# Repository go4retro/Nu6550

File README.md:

# Nu6550

Replacement for the MOS 6550 1kbx4 SRAM using modern components.

## Introduction

## Technical Details

## License
Copyright (C) 2019-20  RETRO Innovations

These files are free designs; you can redistribute them and/or modify
them under the terms of the Creative Commons Attribution-ShareAlike 
4.0 International License.

You should have received a copy of the license along with this
work. If not, see <http://creativecommons.org/licenses/by-sa/4.0/>.

These files are distributed in the hope that they will be useful,
but WITHOUT ANY WARRANTY; without even the implied warranty of
MERCHANTABILITY or FITNESS FOR A PARTICULAR PURPOSE.  See the
license for more details.

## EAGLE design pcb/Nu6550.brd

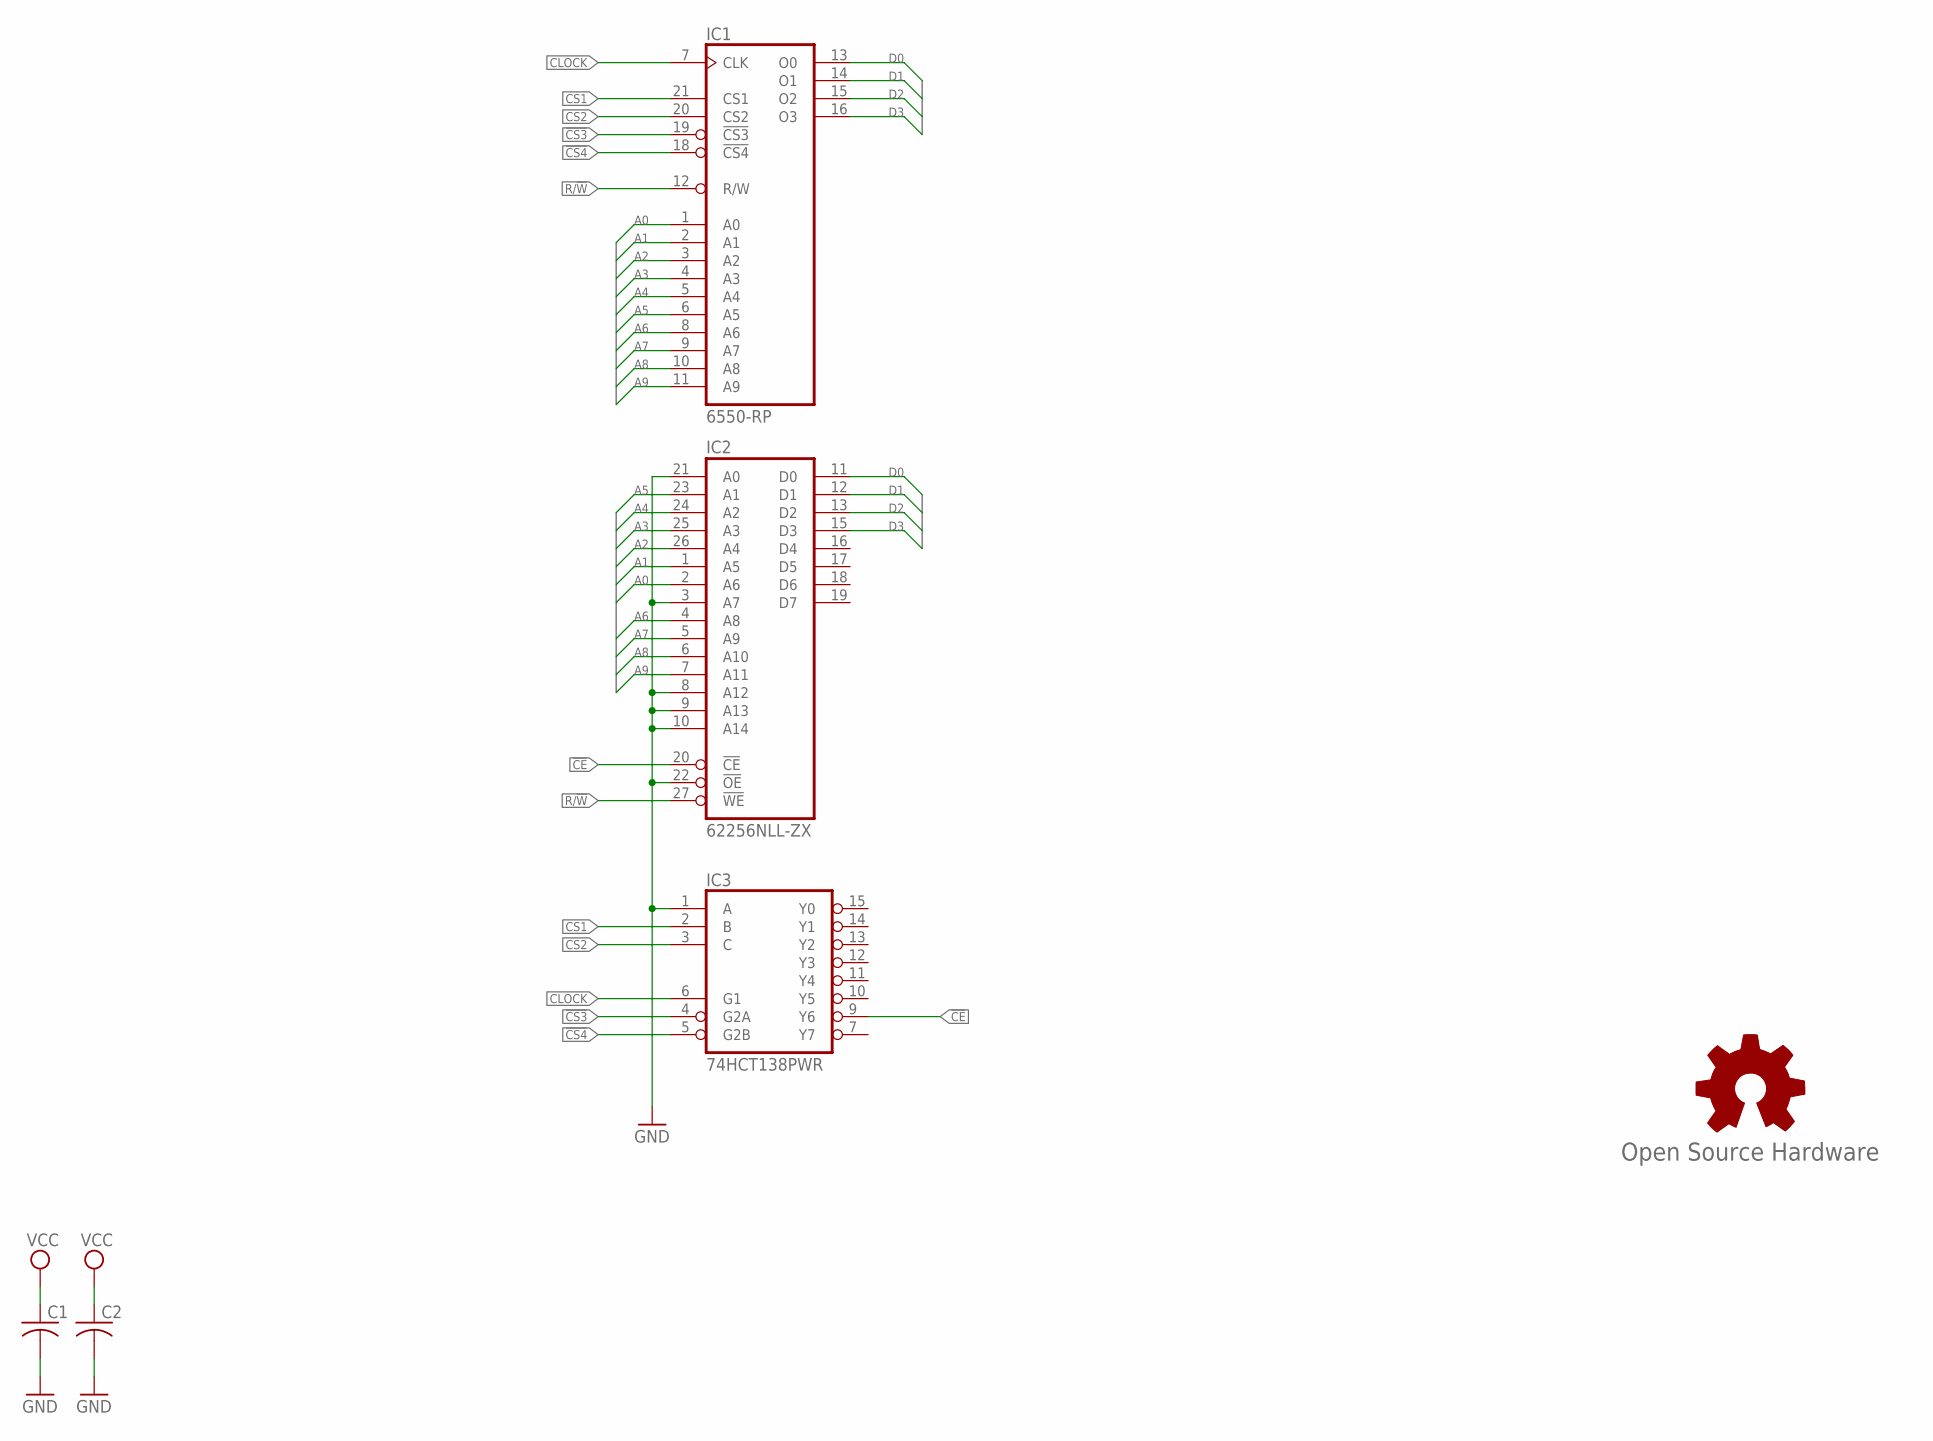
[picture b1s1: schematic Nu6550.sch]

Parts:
C1, C2: C-USC0402; C0402
GOLD_ORB_SM1: Open Source Hardware; OSHW_5MM
IC1: 6550-RP; DIL22/4-ROUNDPAD
IC2: 62256NLL-ZX; TSOP1-28
IC3: 74HCT138PWR; TSSOP16

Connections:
!CE: IC2.20 (!CE), IC3.9 (Y6)
!CS3: IC1.19 (!CS3), IC3.4 (G2A)
!CS4: IC1.18 (!CS4), IC3.5 (G2B)
A0: IC1.1 (A0), IC2.2 (A6)
A1: IC1.2 (A1), IC2.1 (A5)
A2: IC1.3 (A2), IC2.26 (A4)
A3: IC1.4 (A3), IC2.25 (A3)
A4: IC1.5 (A4), IC2.24 (A2)
A5: IC1.6 (A5), IC2.23 (A1)
A6: IC1.8 (A6), IC2.4 (A8)
A7: IC1.9 (A7), IC2.5 (A9)
A8: IC1.10 (A8), IC2.6 (A10)
A9: IC1.11 (A9), IC2.7 (A11)
CLOCK: IC1.7 (CLK), IC3.6 (G1)
CS1: IC1.21 (CS1), IC3.2 (B)
CS2: IC1.20 (CS2), IC3.3 (C)
D0: IC1.13 (O0), IC2.11 (D0)
D1: IC1.14 (O1), IC2.12 (D1)
D2: IC1.15 (O2), IC2.13 (D2)
D3: IC1.16 (O3), IC2.15 (D3)
GND: C1.2, C2.2, IC1.22 (GND), IC2.3 (A7), IC2.8 (A12), IC2.9 (A13), IC2.10 (A14), IC2.14 (GND), IC2.21 (A0), IC2.22 (!OE), IC3.1 (A), IC3.8 (GND)
R/!W: IC1.12 (R/W), IC2.27 (!WE)
VCC: C1.1, C2.1, IC1.17 (VCC), IC2.28 (VCC), IC3.16 (VCC)

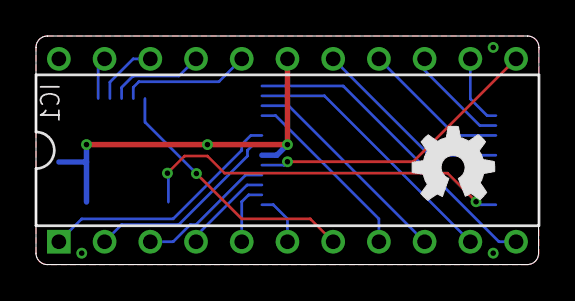
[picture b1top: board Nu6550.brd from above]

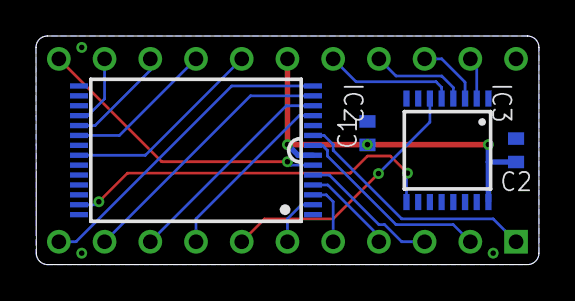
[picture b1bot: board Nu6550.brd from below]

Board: 2 copper layers, 27.9 x 12.7 mm, 6 parts (4 on the bottom side), 23 nets.

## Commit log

2020-11-14 Typo in README.md
